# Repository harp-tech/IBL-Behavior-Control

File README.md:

# IBL Behavior Control (IBL BC)

Repository for the IBL's new behavior control system, based on Harp technology.

# Documentation

Manuals can be found in the folder *Manuals*

# Licensing

The code, designs, documentation, and photos available in this repository is free: you can redistribute it and/or modify it under the terms of the used license.
Each subdirectory will contain a license or, possibly, a set of licenses if it involves both hardware and software. Check files named LICENSE.

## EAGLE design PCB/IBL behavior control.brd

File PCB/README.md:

### Licensing
Copyright Filipe Carvalho 2020

<br />This work is licensed under a <a rel="license" href="http://creativecommons.org/licenses/by-nc-sa/3.0/igo/">Creative Commons Attribution-NonCommercial-ShareAlike 3.0 IGO License</a>.

If your are interested in obtaining a license to sell this device, please contact filipe@open-ephys.org

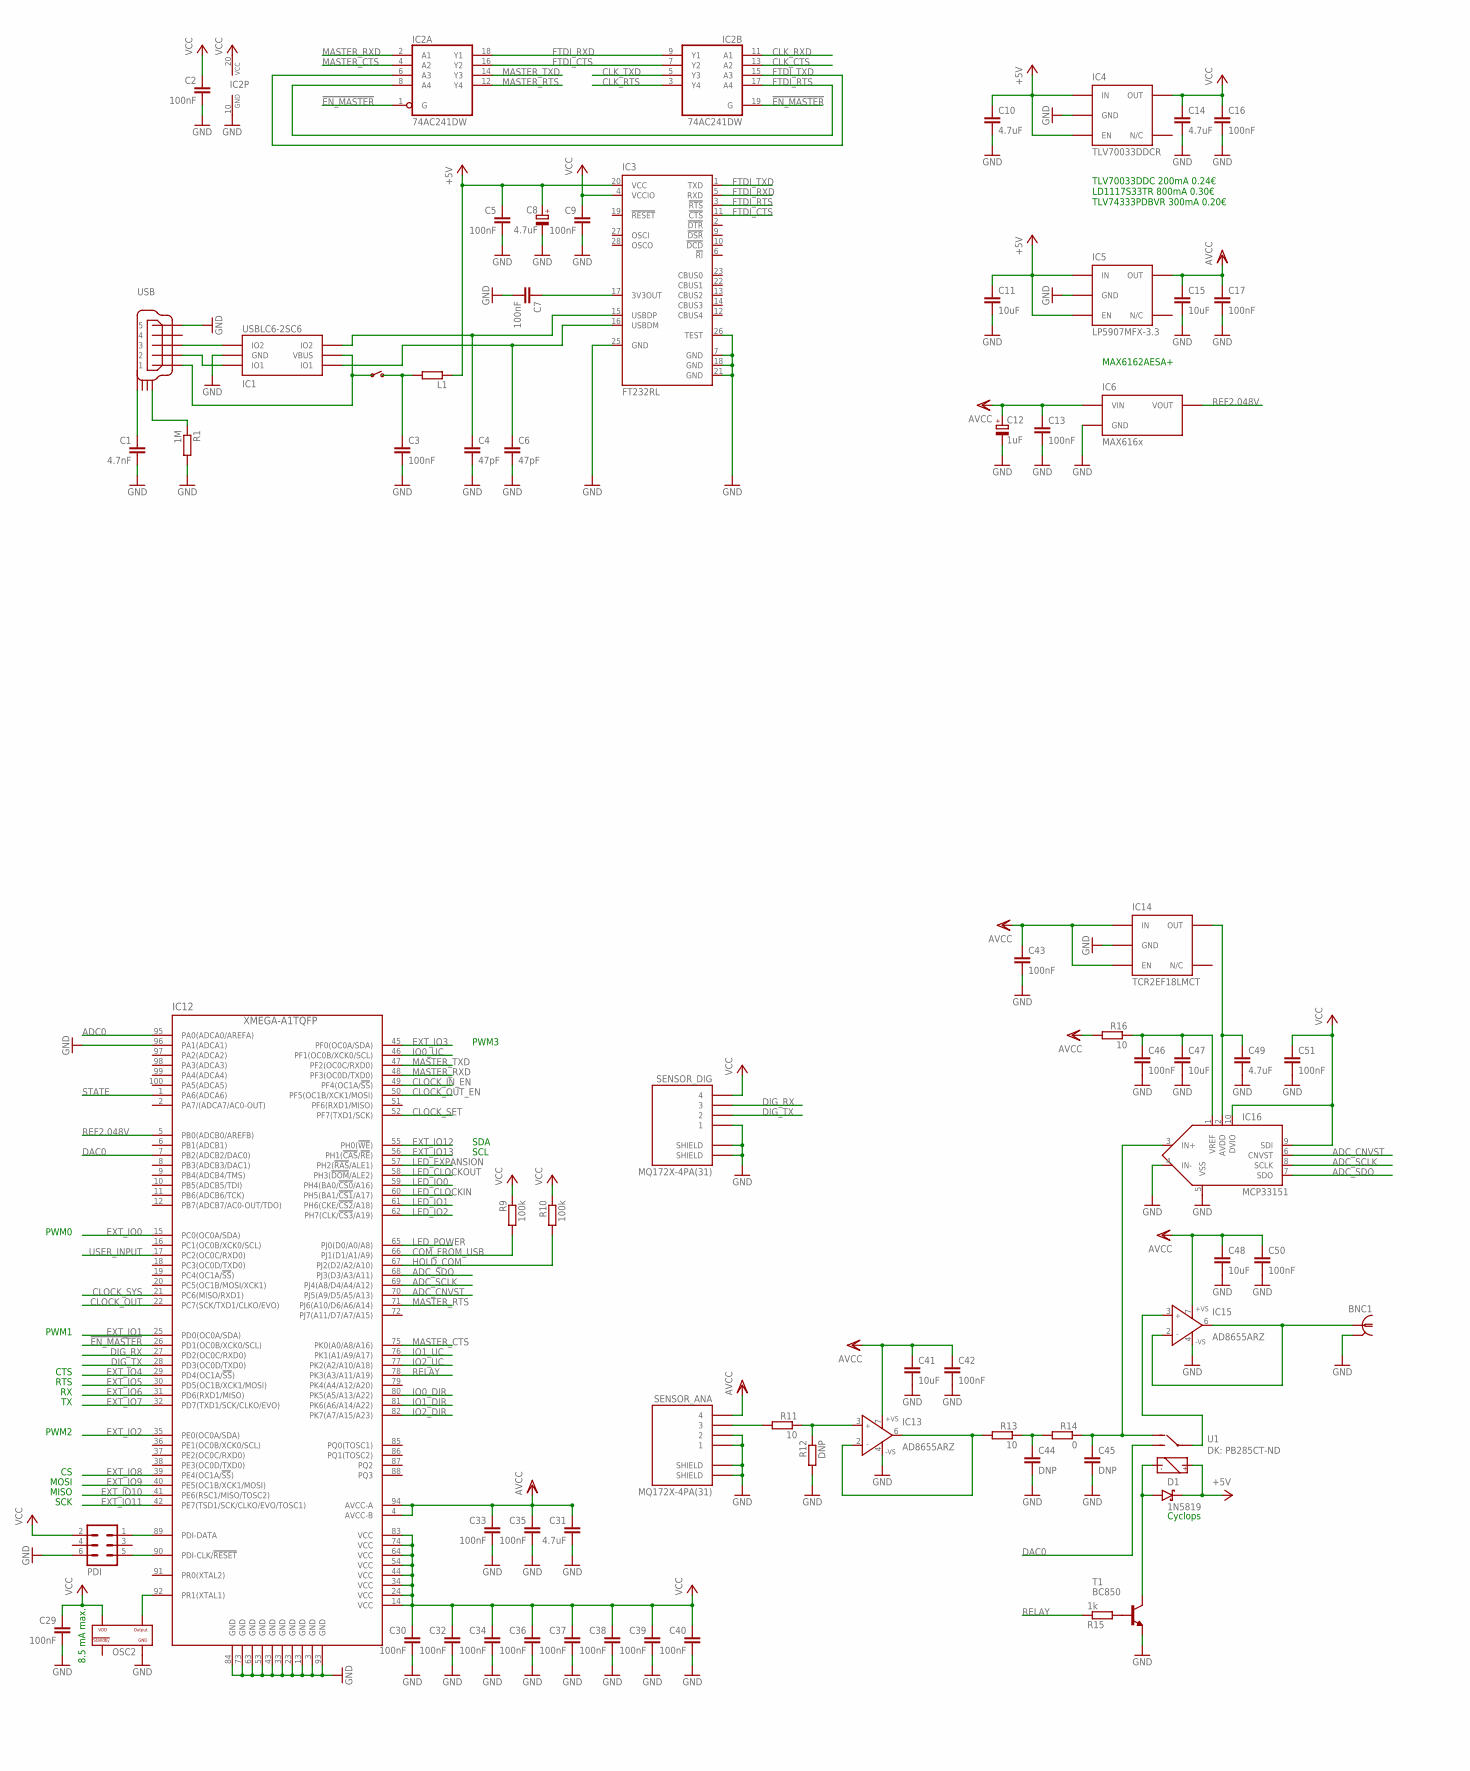
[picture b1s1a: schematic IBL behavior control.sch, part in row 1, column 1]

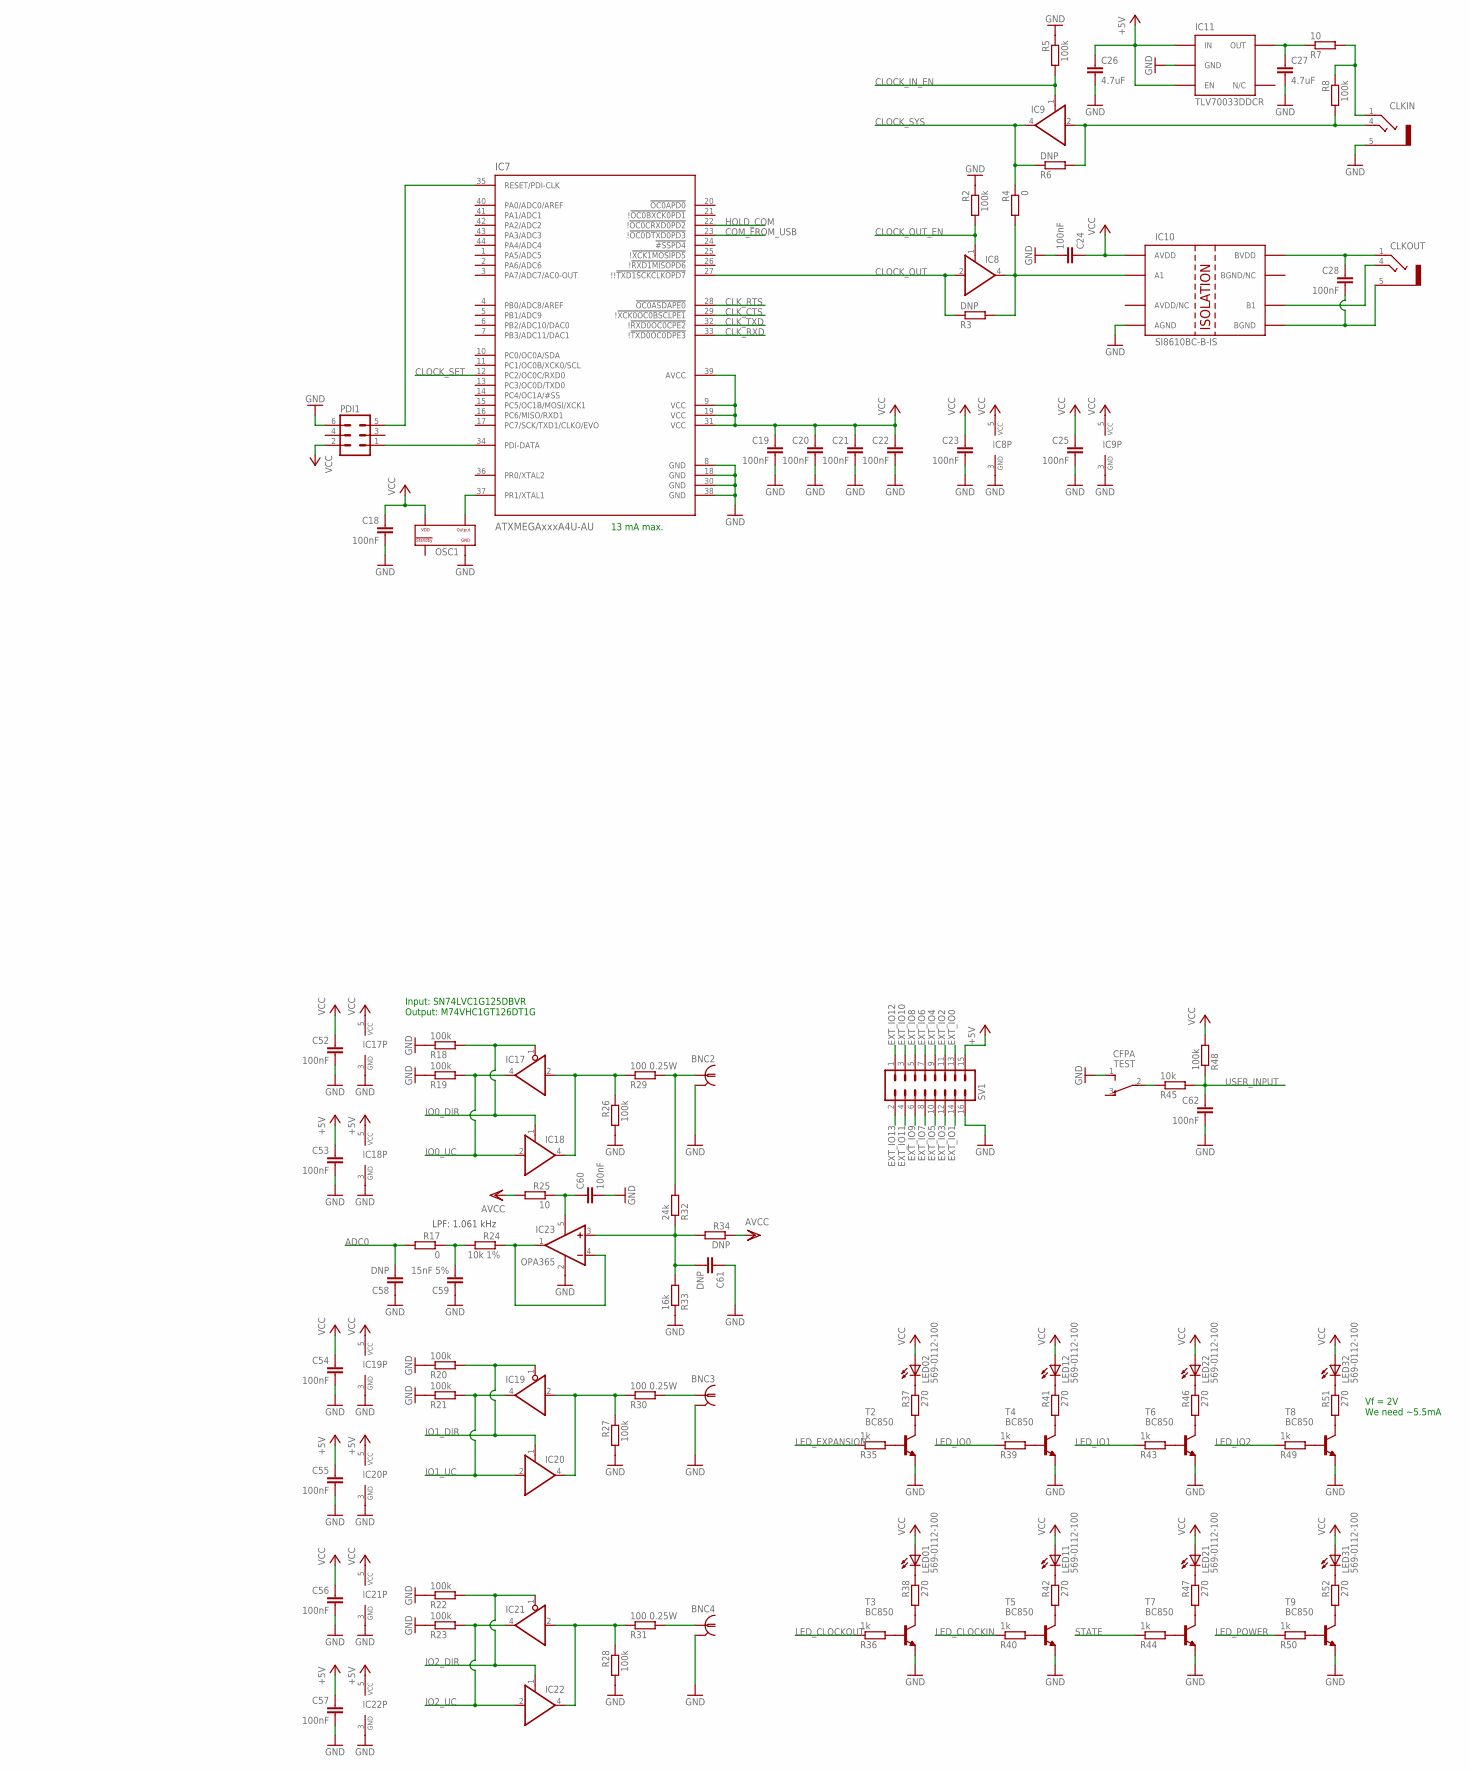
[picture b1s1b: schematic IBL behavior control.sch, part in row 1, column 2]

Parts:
BNC1, BNC2, BNC3, BNC4: BNC_0731000105; 0731000105
C1: 4.7nF; C0402
C2, C3, C5, C7, C9, C13, C16, C17, C18, C19, C20, C21, C22, C23, C24, C25, C28, C29, C30, C32, C33, C34, C35, C36, C37, C38, C39, C40, C42, C43, C46, C50, C51, C52, C53, C54, C55, C56, C57, C60, C62: 100nF; C0402
C4, C6: 47pF; C0402
C8: 4.7uF; A/3216-18W
C10, C14, C26, C27, C31, C49: 4.7uF; C0603
C11, C15, C41, C47, C48: 10uF; C0603
C12: 1uF; R/2012-12R
C44, C45, C58, C61: DNP; C0402
C59: 15nF 5%; C0402
CLKIN: STEREO_JACK; 35RASMT2BHNTRX
CLKOUT: STEREO_JACK; 35RASMT2BHNTRX
D1: 1N5819; SOD123
IC1: USBLC6-2SC6; SOT23-6L
IC2: 74AC241DW; SO20W
IC3: FT232RL; SSOP28
IC4, IC11: TLV70033DDCR; TSOT23-5
IC5: LP5907MFX-3.3; TSOT23-5
IC6: MAX616x; SO-08
IC7: ATXMEGAxxxA4U-AU; QFP80P1200X1200X120-44N
IC8, IC9, IC18, IC20, IC22: 74AHC1G126DCK; SC70-5
IC10: SI8610BC-B-IS; SO-08
IC12: XMEGA-A1TQFP; TQFP100
IC13, IC15: AD8655ARZ; SO8
IC14: TCR2EF18LMCT; TSOT23-5
IC16: MCP33151; MSOP10
IC17, IC19, IC21: 74AHC1G125DBV; SOT23-5
IC23: OPA365; SOT23-5
L1: ???; R0805
LED0, LED1, LED2, LED3: 569-0112-100; 569-011X-X00_LED_ARRAY
OSC1, OSC2: OSCILLATOR; OSCILLATOR_3.2X2.5
PDI, PDI1: MA03-2
R1: 1M; R0402
R2, R5, R8, R9, R10, R18, R19, R20, R21, R22, R23, R26, R27, R28, R48: 100k; R0402
R3, R6, R12, R34: DNP; R0402
R4, R14, R17: 0; R0402
R7, R11, R13, R16, R25: 10; R0402
R15, R35, R36, R39, R40, R43, R44, R49, R50: 1k; R0402
R24: 10k 1%; R0402
R29, R30, R31: 100 0.25W; R0603
R32: 24k; R0402
R33: 16k; R0402
R37, R38, R41, R42, R46, R47, R51, R52: 270; R0402
R45: 10k; R0402
SENSOR_ANA: MQ172X-4PA(31)
SENSOR_DIG: MQ172X-4PA(31)
SV1: ML16L
T1, T2, T3, T4, T5, T6, T7, T8, T9: BC850; SOT23
TEST: CFPA
U1: DK: PB285CT-ND; RELAY
USB: USB_MINI_B; 240-0002-1

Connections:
5VSWITCH: C3.1, L1.2
5VUSB: IC1.P$5 (VBUS), USB.P$1 (1)
!EN_MASTER: IC2.1 (G), IC2.19 (G), IC12.26 (PD1(OC0B/XCK0/SCL))
+5V: C5.1, C8.+, C10.1, C11.1, C26.1, C53.1, C55.1, C57.1, D1.C, IC3.20 (VCC), IC4.1 (IN), IC4.3 (EN), IC5.1 (IN), IC5.3 (EN), IC11.1 (IN), IC11.3 (EN), IC18.5 (VCC), IC20.5 (VCC), IC22.5 (VCC), L1.1, SV1.15, U1.3 (R+)
ADC0: C58.2, IC12.95 (PA0(ADCA0/AREFA)), R17.2
ADC_CNVST: IC12.70 (PJ5(A9/D5/A5/A13)), IC16.6 (CNVST)
ADC_SCLK: IC12.69 (PJ4(A8/D4/A4/A12)), IC16.8 (SCLK)
ADC_SDO: IC12.68 (PJ3(D3/A3/A11)), IC16.7 (SDO)
CLK_CTS: IC2.13 (A2), IC7.29 (!!XCK0OC0BSCLPE1)
CLK_RTS: IC2.3 (Y4), IC7.28 (!OC0ASDAPE0)
CLK_RXD: IC2.11 (A1), IC7.33 (!!TXD0OC0DPE3)
CLK_TXD: IC2.5 (Y3), IC7.32 (!!RXD0OC0CPE2)
CLOCK_IN_EN: IC9.1 (OE), IC12.49 (PF4(OC1A/!SS!)), R5.2
CLOCK_OUT: IC7.27 (!!!TXD1SCKCLKOPD7), IC8.2 (I), IC12.22 (PC7(SCK/TXD1/CLKO/EVO)), R3.1
CLOCK_OUT_EN: IC8.1 (OE), IC12.50 (PF5(OC1B/XCK1/MOSI)), R2.2
CLOCK_SET: IC7.12 (PC2/OC0C/RXD0), IC12.52 (PF7(TXD1/SCK))
CLOCK_SYS: IC9.4 (O), IC12.21 (PC6(MISO/RXD1)), R4.1, R6.1
COM_FROM_USB: IC7.23 (!!OC0DTXD0PD3), IC12.66 (PJ1(D1/A1/A9)), R9.2
DAC0: IC12.7 (PB2(ADCB2/DAC0)), U1.10 (NO)
DIG_RX: IC12.27 (PD2(OC0C/RXD0)), SENSOR_DIG.3
DIG_TX: IC12.28 (PD3(OC0D/TXD0)), SENSOR_DIG.2
EXT_IO0: IC12.15 (PC0(OC0A/SDA)), SV1.13
EXT_IO1: IC12.25 (PD0(OC0A/SDA)), SV1.14
EXT_IO2: IC12.35 (PE0(OC0A/SDA)), SV1.11
EXT_IO3: IC12.45 (PF0(OC0A/SDA)), SV1.12
EXT_IO4: IC12.29 (PD4(OC1A/!SS!)), SV1.9
EXT_IO5: IC12.30 (PD5(OC1B/XCK1/MOSI)), SV1.10
EXT_IO6: IC12.31 (PD6(RXD1/MISO)), SV1.7
EXT_IO7: IC12.32 (PD7(TXD1/SCK/CLKO/EVO)), SV1.8
EXT_IO8: IC12.39 (PE4(OC1A/!SS!)), SV1.5
EXT_IO9: IC12.40 (PE5(OC1B/XCK1/MOSI)), SV1.6
EXT_IO10: IC12.41 (PE6(RSC1/MISO/TOSC2)), SV1.3
EXT_IO11: IC12.42 (PE7(TSD1/SCK/CLKO/EVO/TOSC1)), SV1.4
EXT_IO12: IC12.55 (PH0(!WE!)), SV1.1
EXT_IO13: IC12.56 (PH1(!CAS!/!RE!)), SV1.2
FTDI_CTS: IC2.7 (Y2), IC2.16 (Y2), IC3.11 (!CTS)
FTDI_RTS: IC2.8 (A4), IC2.17 (A4), IC3.3 (!RTS)
FTDI_RXD: IC2.9 (Y1), IC2.18 (Y1), IC3.5 (RXD)
FTDI_TXD: IC2.6 (A3), IC2.15 (A3), IC3.1 (TXD)
GND: BNC1.2, BNC1.3 (2), BNC2.2, BNC2.3 (2), BNC3.2, BNC3.3 (2), BNC4.2, BNC4.3 (2), C1.2, C2.2, C3.2, C4.2, C5.2, C6.2, C7.2, C8.-, C9.2, C10.2, C11.2, C12.-, C13.2, C14.2, C15.2, C16.2, C17.2, C18.2, C19.2, C20.2, C21.2, C22.2, C23.2, C24.2, C25.2, C26.2, C27.2, C29.2, C30.2, C31.2, C32.2, C33.2, C34.2, C35.2, C36.2, C37.2, C38.2, C39.2, C40.2, C41.2, C42.2, C43.2, C44.2, C45.2, C46.2, C47.2, C48.2, C49.2, C50.2, C51.2, C52.2, C53.2, C54.2, C55.2, C56.2, C57.2, C58.1, C59.1, C60.2, C61.1, C62.2, CLKIN.5, IC1.P$2 (GND), IC2.10 (GND), IC3.7 (GND), IC3.18 (GND), IC3.21 (GND), IC3.25 (GND), IC3.26 (TEST), IC4.2 (GND), IC5.2 (GND), IC6.4 (GND), IC7.8 (GND), IC7.18 (GND), IC7.30 (GND), IC7.38 (GND), IC8.3 (GND), IC9.3 (GND), IC10.4 (AGND), IC11.2 (GND), IC12.3 (GND), IC12.13 (GND), IC12.23 (GND), IC12.33 (GND), IC12.43 (GND), IC12.53 (GND), IC12.63 (GND), IC12.73 (GND), IC12.84 (GND), IC12.93 (GND), IC12.96 (PA1(ADCA1)), IC13.4 (-VS), IC14.2 (GND), IC15.4 (-VS), IC16.4 (IN-), IC16.5 (VSS), IC17.3 (GND), IC18.3 (GND), IC19.3 (GND), IC20.3 (GND), IC21.3 (GND), IC22.3 (GND), IC23.2 (V-), OSC1.P$2 (GND), OSC2.P$2 (GND), PDI.6, PDI1.6, R1.2, R2.1, R5.1, R12.2, R18.1, R19.1, R20.1, R21.1, R22.1, R23.1, R26.2, R27.2, R28.2, R33.1, SENSOR_ANA.1, SENSOR_ANA.2, SENSOR_ANA.SHIELD1 (SHIELD), SENSOR_ANA.SHIELD2 (SHIELD), SENSOR_DIG.1, SENSOR_DIG.SHIELD1 (SHIELD), SENSOR_DIG.SHIELD2 (SHIELD), SV1.16, T1.2 (E), T2.2 (E), T3.2 (E), T4.2 (E), T5.2 (E), T6.2 (E), T7.2 (E), T8.2 (E), T9.2 (E), TEST.1 (3), USB.P$5 (5)
GND_ISO: C28.2, CLKOUT.5, IC10.5 (BGND)
HOLD_COM: IC7.22 (!!OC0CRXD0PD2), IC12.67 (PJ2(D2/A2/A10)), R10.2
IO0_ANALOG: C59.2, R17.1, R24.2
IO0_DIR: IC12.80 (PK5(A5/A13/A22)), IC17.1 (OE), IC18.1 (OE), R18.2
IO0_UC: IC12.46 (PF1(OC0B/XCK0/SCL)), IC17.4 (O), IC18.2 (I), R19.2
IO1_DIR: IC12.81 (PK6(A6/A14/A22)), IC19.1 (OE), IC20.1 (OE), R20.2
IO1_UC: IC12.76 (PK1(A1/A9/A17)), IC19.4 (O), IC20.2 (I), R21.2
IO2_DIR: IC12.82 (PK7(A7/A15/A23)), IC21.1 (OE), IC22.1 (OE), R22.2
IO2_UC: IC12.77 (PK2(A2/A10/A18)), IC21.4 (O), IC22.2 (I), R23.2
LED_CLOCKIN: IC12.60 (PH5(BA1/!CS1!/A17)), R40.1
LED_CLOCKOUT: IC12.58 (PH3(!DOM!/ALE2)), R36.1
LED_EXPANSION: IC12.57 (PH2(!RAS!/ALE1)), R35.1
LED_IO0: IC12.59 (PH4(BA0/!CS0!/A16)), R39.1
LED_IO1: IC12.61 (PH6(CKE/!CS2!/A18)), R43.1
LED_IO2: IC12.62 (PH7(CLK/!CS3!/A19)), R49.1
LED_POWER: IC12.65 (PJ0(D0/A0/A8)), R50.1
MASTER_CTS: IC2.4 (A2), IC12.75 (PK0(A0/A8/A16))
MASTER_RTS: IC2.12 (Y4), IC12.71 (PJ6(A10/D6/A6/A14))
MASTER_RXD: IC2.2 (A1), IC12.48 (PF3(OC0D/TXD0))
MASTER_TXD: IC2.14 (Y3), IC12.47 (PF2(OC0C/RXD0))
unnamed: CLKOUT.4, IC10.6 (B1)
unnamed: R35.2, T2.1 (B)
unnamed: LED0.C2 (C), R37.1
unnamed: C28.1, CLKOUT.1, IC10.8 (BVDD)
unnamed: IC17.2 (I), IC18.4 (O), R26.1, R29.1
unnamed: R37.2, T2.3 (C)
unnamed: BNC2.1, R29.2, R32.2
unnamed: IC19.2 (I), IC20.4 (O), R27.1, R30.1
unnamed: BNC3.1, R30.2
unnamed: IC21.2 (I), IC22.4 (O), R28.1, R31.1
unnamed: BNC4.1, R31.2
unnamed: R36.2, T3.1 (B)
unnamed: R43.2, T6.1 (B)
unnamed: R38.2, T3.3 (C)
unnamed: R39.2, T4.1 (B)
unnamed: LED3.C1 (C), R52.1
unnamed: R41.2, T4.3 (C)
unnamed: R40.2, T5.1 (B)
unnamed: R46.2, T6.3 (C)
unnamed: R42.2, T5.3 (C)
unnamed: LED3.C2 (C), R51.1
unnamed: R44.2, T7.1 (B)
unnamed: R47.2, T7.3 (C)
unnamed: R49.2, T8.1 (B)
unnamed: R51.2, T8.3 (C)
unnamed: R50.2, T9.1 (B)
unnamed: R52.2, T9.3 (C)
unnamed: LED1.C2 (C), R41.1
unnamed: LED2.C2 (C), R46.1
unnamed: LED1.C1 (C), R42.1
unnamed: LED2.C1 (C), R47.1
unnamed: R45.1, TEST.2
unnamed: C60.1, IC23.5 (V+), R25.1
unnamed: LED0.C1 (C), R38.1
unnamed: IC13.2 (IN-), IC13.6 (OUT), R13.2
unnamed: C7.1, IC3.17 (3V3OUT)
unnamed: IC13.3 (IN+), R11.1, R12.1
unnamed: IC1.P$1 (IO1), USB.P$2 (2)
unnamed: CLKIN.1, R7.2, R8.1
unnamed: C27.1, IC11.5 (OUT), R7.1
unnamed: IC8.4 (O), IC10.2 (A1), R3.2, R4.2
unnamed: C49.1, IC14.5 (OUT), IC16.2 (AVDD)
unnamed: C44.1, R13.1, R14.2
unnamed: C45.1, IC16.3 (IN+), R14.1, U1.1 (NC)
unnamed: BNC1.1, IC15.2 (IN-), IC15.6 (OUT)
unnamed: C46.1, C47.1, IC16.1 (VREF), R16.1
unnamed: IC1.P$3 (IO2), USB.P$3 (3)
unnamed: IC15.3 (IN+), U1.5 (IN)
unnamed: R11.2, SENSOR_ANA.3
unnamed: R15.2, T1.1 (B)
unnamed: D1.A, T1.3 (C), U1.8 (R-)
unnamed: IC23.1 (OUT), IC23.4 (-IN), R24.1
unnamed: C1.1, USB.SHIELD_4
unnamed: R1.1, USB.SHIELD_1
unnamed: C61.2, IC23.3 (+IN), R32.1, R33.2, R34.2
OSC1: IC12.92 (PR1(XTAL1)), OSC2.P$3 (OUTPUT)
OSC2: IC7.37 (PR1/XTAL1), OSC1.P$3 (OUTPUT)
PDI-CLK: IC7.35 (RESET/PDI-CLK), PDI1.5
PDI-DATA: IC7.34 (PDI-DATA), PDI1.1
PDI_CLK: IC12.90 (PDI-CLK/!RESET), PDI.5
PDI_DATA: IC12.89 (PDI-DATA), PDI.1
REF2.048V: IC6.6 (VOUT), IC12.5 (PB0(ADCB0/AREFB))
RELAY: IC12.78 (PK3(A3/A11/A19)), R15.1
STATE: IC12.1 (PA6(ADCA6)), R44.1
SYNCIN: CLKIN.4, IC9.2 (I), R6.2, R8.2
USBDM: C6.1, IC1.P$6 (IO1), IC3.16 (USBDM)
USBDP: C4.1, IC1.P$4 (IO2), IC3.15 (USBDP)
USER_INPUT: C62.1, IC12.17 (PC2(OC0C/RXD0)), R45.2, R48.1
VCC: C2.1, C9.1, C14.1, C16.1, C18.1, C19.1, C20.1, C21.1, C22.1, C23.1, C24.1, C25.1, C29.1, C30.1, C32.1, C34.1, C36.1, C37.1, C38.1, C39.1, C40.1, C51.1, C52.1, C54.1, C56.1, IC2.20 (VCC), IC3.4 (VCCIO), IC4.5 (OUT), IC7.9 (VCC), IC7.19 (VCC), IC7.31 (VCC), IC7.39 (AVCC), IC8.5 (VCC), IC9.5 (VCC), IC10.1 (AVDD), IC12.14 (VCC), IC12.24 (VCC), IC12.34 (VCC), IC12.44 (VCC), IC12.54 (VCC), IC12.64 (VCC), IC12.74 (VCC), IC12.83 (VCC), IC16.9 (SDI), IC16.10 (DVIO), IC17.5 (VCC), IC19.5 (VCC), IC21.5 (VCC), LED0.A1 (A), LED0.A2 (A), LED1.A1 (A), LED1.A2 (A), LED2.A1 (A), LED2.A2 (A), LED3.A1 (A), LED3.A2 (A), OSC1.P$4 (VDD), OSC2.P$4 (VDD), PDI.2, PDI1.2, R9.1, R10.1, R48.2, SENSOR_DIG.4
VDD: C12.+, C13.1, C15.1, C17.1, C31.1, C33.1, C35.1, C41.1, C42.1, C43.1, C48.1, C50.1, IC5.5 (OUT), IC6.2 (VIN), IC12.4 (AVCC-B), IC12.94 (AVCC-A), IC13.7 (+VS), IC14.1 (IN), IC14.3 (EN), IC15.7 (+VS), R16.2, R25.2, R34.1, SENSOR_ANA.4

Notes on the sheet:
RTS
CTS
PWM2
PWM1
MOSI
MISO
SCK
PWM0
PWM3
SDA
SCL
Input: SN74LVC1G125DBVR Output: M74VHC1GT126DT1G
Vf = 2V We need ~5.5mA
8.5 mA max.
13 mA max.
TLV70033DDC 200mA 0.24€ LD1117S33TR 800mA 0.30€ TLV74333PDBVR 300mA 0.20€
LPF: 1.061 kHz
MAX6162AESA+
Cyclops

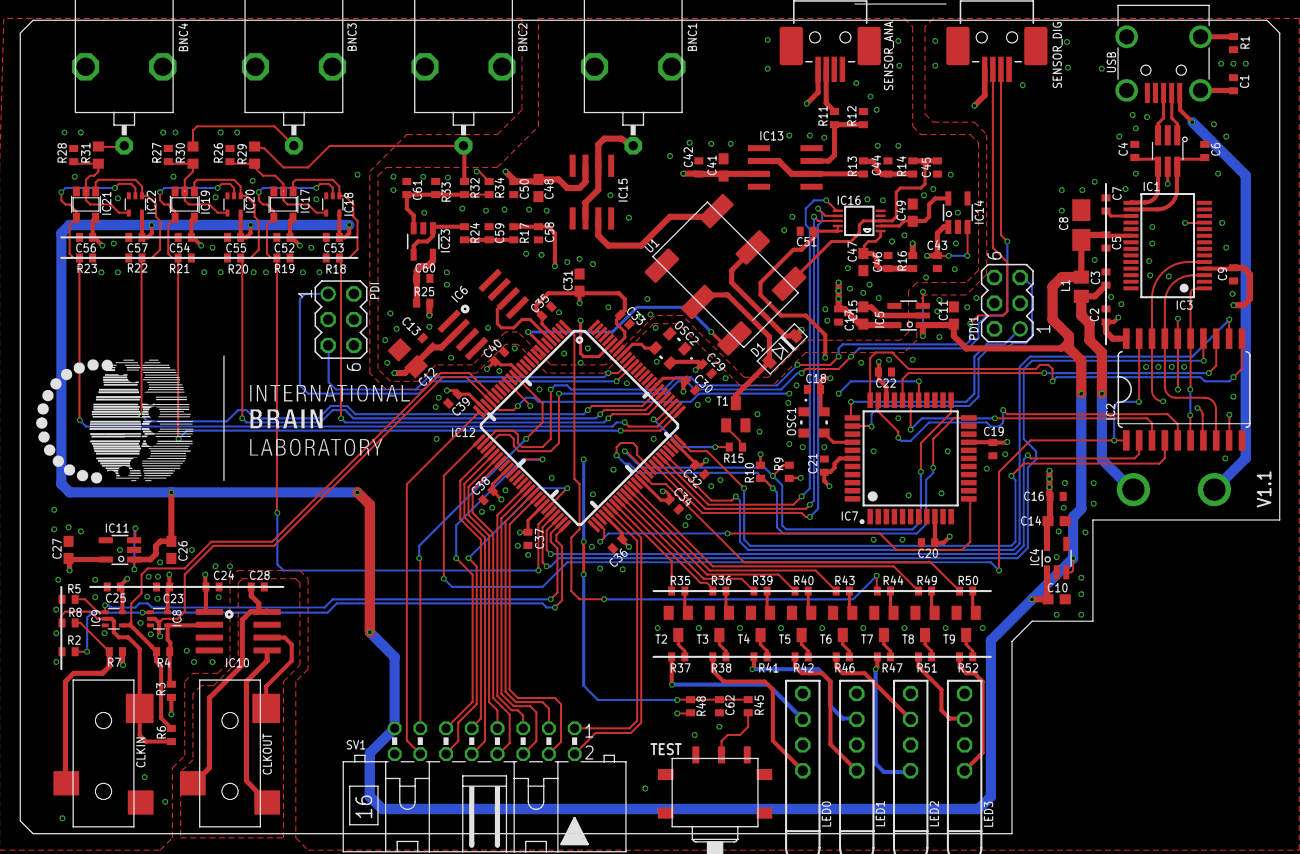
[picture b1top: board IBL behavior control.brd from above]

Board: 4 copper layers, 124.5 x 80.4 mm, 168 parts (0 on the bottom side), 130 nets.

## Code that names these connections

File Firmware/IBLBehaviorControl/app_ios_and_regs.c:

#include <avr/io.h>
#include "hwbp_core_types.h"
#include "app_ios_and_regs.h"

/************************************************************************/
/* Configure and initialize IOs                                         */
/************************************************************************/
void init_ios(void)
{	/* Configure input pins */
	io_pin2in(&PORTJ, 3, PULL_IO_TRISTATE, SENSE_IO_EDGES_BOTH);         // ADC_SDO
	io_pin2in(&PORTC, 2, PULL_IO_TRISTATE, SENSE_IO_EDGES_BOTH);         // USER
	io_pin2in(&PORTF, 1, PULL_IO_TRISTATE, SENSE_IO_EDGES_BOTH);         // IO0
	io_pin2in(&PORTK, 1, PULL_IO_TRISTATE, SENSE_IO_EDGES_BOTH);         // IO1
	io_pin2in(&PORTK, 2, PULL_IO_TRISTATE, SENSE_IO_EDGES_BOTH);         // IO2

	/* Configure input interrupts */
	io_set_int(&PORTC, INT_LEVEL_LOW, 0, (1<<2), false);                 // USER
	io_set_int(&PORTF, INT_LEVEL_LOW, 0, (1<<1), false);                 // IO0
	io_set_int(&PORTK, INT_LEVEL_LOW, 0, (1<<1), false);                 // IO1
	io_set_int(&PORTK, INT_LEVEL_LOW, 1, (1<<2), false);                 // IO2

	/* Configure output pins */
	io_pin2out(&PORTF, 4, OUT_IO_DIGITAL, IN_EN_IO_EN);                  // CLOCK_IN_EN
	io_pin2out(&PORTF, 5, OUT_IO_DIGITAL, IN_EN_IO_EN);                  // CLOCK_OUT_EN
	io_pin2out(&PORTK, 3, OUT_IO_DIGITAL, IN_EN_IO_EN);                  // RELAY
	io_pin2out(&PORTJ, 4, OUT_IO_DIGITAL, IN_EN_IO_EN);                  // ADC_SCLK
	io_pin2out(&PORTJ, 5, OUT_IO_DIGITAL, IN_EN_IO_EN);                  // ADC_CNVST
	io_pin2out(&PORTD, 1, OUT_IO_DIGITAL, IN_EN_IO_EN);                  // EN_MASTER
	io_pin2out(&PORTH, 2, OUT_IO_DIGITAL, IN_EN_IO_EN);                  // LED_CLKIN
	io_pin2out(&PORTH, 4, OUT_IO_DIGITAL, IN_EN_IO_EN);                  // LED_IO0
	io_pin2out(&PORTH, 6, OUT_IO_DIGITAL, IN_EN_IO_EN);                  // LED_IO1
	io_pin2out(&PORTH, 7, OUT_IO_DIGITAL, IN_EN_IO_EN);                  // LED_IO2
	io_pin2out(&PORTH, 3, OUT_IO_DIGITAL, IN_EN_IO_EN);                  // LED_SLAVE
	io_pin2out(&PORTH, 5, OUT_IO_DIGITAL, IN_EN_IO_EN);                  // LED_MASTER
	io_pin2out(&PORTA, 6, OUT_IO_DIGITAL, IN_EN_IO_EN);                  // LED_STATE
	io_pin2out(&PORTJ, 0, OUT_IO_DIGITAL, IN_EN_IO_EN);                  // LED_POWER
	io_pin2out(&PORTF, 1, OUT_IO_DIGITAL, IN_EN_IO_EN);                  // IO0
	io_pin2out(&PORTK, 1, OUT_IO_DIGITAL, IN_EN_IO_EN);                  // IO1
	io_pin2out(&PORTK, 2, OUT_IO_DIGITAL, IN_EN_IO_EN);                  // IO2
	io_pin2out(&PORTK, 5, OUT_IO_DIGITAL, IN_EN_IO_EN);                  // IO0_DIR
	io_pin2out(&PORTK, 6, OUT_IO_DIGITAL, IN_EN_IO_EN);                  // IO1_DIR
	io_pin2out(&PORTK, 7, OUT_IO_DIGITAL, IN_EN_IO_EN);                  // IO2_DIR

	/* Initialize output pins */
	clr_CLOCK_IN_EN;
	clr_CLOCK_OUT_EN;
	clr_RELAY;
	clr_ADC_SCLK;
	clr_ADC_CNVST;
	clr_EN_MASTER;
	clr_LED_CLKIN;
	clr_LED_IO0;
	clr_LED_IO1;
	clr_LED_IO2;
	clr_LED_SLAVE;
	clr_LED_MASTER;
	clr_LED_STATE;
	clr_LED_POWER;
	clr_IO0;
	clr_IO1;
	clr_IO2;
	clr_IO0_DIR;
	clr_IO1_DIR;
	clr_IO2_DIR;
}

/************************************************************************/
/* Registers' stuff                                                     */
/************************************************************************/
AppRegs app_regs;

uint8_t app_regs_type[] = {
	TYPE_U16,
	TYPE_I16,
	TYPE_U8,
	TYPE_U8,
	TYPE_U8,
	TYPE_U8,
	TYPE_U8,
	TYPE_U8,
	TYPE_U8,
	TYPE_U8,
	TYPE_U16,
	TYPE_U16,
	TYPE_U16,
	TYPE_U16,
	TYPE_U8,
	TYPE_U16,
	TYPE_U16,
	TYPE_U16,
	TYPE_U16,
	TYPE_U8,
	TYPE_U16,
	TYPE_U16,
	TYPE_U16,
	TYPE_U16,
	TYPE_U8,
	TYPE_U16,
	TYPE_U16,
	TYPE_U16,
	TYPE_U16,
	TYPE_U8,
	TYPE_I16,
	TYPE_U16,
	TYPE_I16,
	TYPE_U16,
	TYPE_U8,
	TYPE_I16,
	TYPE_U16,
	TYPE_I16,
	TYPE_U16,
	TYPE_U8,
	TYPE_U8,
	TYPE_U16,
	TYPE_I16
};

uint16_t app_regs_n_elements[] = {
	1,
	4,
	1,
	1,
	1,
	1,
	1,
	1,
	1,
	1,
	1,
	1,
	1,
	1,
	1,
	1,
	1,
	1,
	1,
	1,
	1,
	1,
	1,
	1,
	1,
	1,
	1,
	1,
	1,
	1,
	1,
	1,
	1,
	1,
	1,
	1,
	1,
	1,
	1,
	1,
	1,
	1,
	1
};

uint8_t *app_regs_pointer[] = {
	(uint8_t*)(&app_regs.REG_CONFIG),
	(uint8_t*)(app_regs.REG_DATA_STREAM),
	(uint8_t*)(&app_regs.REG_INPUTS),
	(uint8_t*)(&app_regs.REG_INPUT_IO0_CONFIG),
	(uint8_t*)(&app_regs.REG_INPUT_IO1_CONFIG),
	(uint8_t*)(&app_regs.REG_INPUT_IO2_CONFIG),
	(uint8_t*)(&app_regs.REG_OUTPUT_SET),
	(uint8_t*)(&app_regs.REG_OUTPUT_CLEAR),
	(uint8_t*)(&app_regs.REG_OUTPUT_TOGGLE),
	(uint8_t*)(&app_regs.REG_OUTPUT_WRITE),
	(uint8_t*)(&app_regs.REG_ANA_SENSOR_TH0_HIGH),
	(uint8_t*)(&app_regs.REG_ANA_SENSOR_TH0_HIGH_MS),
	(uint8_t*)(&app_regs.REG_ANA_SENSOR_TH0_LOW),
	(uint8_t*)(&app_regs.REG_ANA_SENSOR_TH0_LOW_MS),
	(uint8_t*)(&app_regs.REG_ANA_SENSOR_TH0_EVT_CONF),
	(uint8_t*)(&app_regs.REG_ANA_SENSOR_TH1_HIGH),
	(uint8_t*)(&app_regs.REG_ANA_SENSOR_TH1_HIGH_MS),
	(uint8_t*)(&app_regs.REG_ANA_SENSOR_TH1_LOW),
	(uint8_t*)(&app_regs.REG_ANA_SENSOR_TH1_LOW_MS),
	(uint8_t*)(&app_regs.REG_ANA_SENSOR_TH1_EVT_CONF),
	(uint8_t*)(&app_regs.REG_ANA_INPUT_TH0_HIGH),
	(uint8_t*)(&app_regs.REG_ANA_INPUT_TH0_HIGH_MS),
	(uint8_t*)(&app_regs.REG_ANA_INPUT_TH0_LOW),
	(uint8_t*)(&app_regs.REG_ANA_INPUT_TH0_LOW_MS),
	(uint8_t*)(&app_regs.REG_ANA_INPUT_TH0_EVT_CONF),
	(uint8_t*)(&app_regs.REG_ANA_INPUT_TH1_HIGH),
	(uint8_t*)(&app_regs.REG_ANA_INPUT_TH1_HIGH_MS),
	(uint8_t*)(&app_regs.REG_ANA_INPUT_TH1_LOW),
	(uint8_t*)(&app_regs.REG_ANA_INPUT_TH1_LOW_MS),
	(uint8_t*)(&app_regs.REG_ANA_INPUT_TH1_EVT_CONF),
	(uint8_t*)(&app_regs.REG_ENCODER_TH0_HIGH),
	(uint8_t*)(&app_regs.REG_ENCODER_TH0_HIGH_MS),
	(uint8_t*)(&app_regs.REG_ENCODER_TH0_LOW),
	(uint8_t*)(&app_regs.REG_ENCODER_TH0_LOW_MS),
	(uint8_t*)(&app_regs.REG_ENCODER_TH0_EVT_CONF),
	(uint8_t*)(&app_regs.REG_ENCODER_TH1_HIGH),
	(uint8_t*)(&app_regs.REG_ENCODER_TH1_HIGH_MS),
	(uint8_t*)(&app_regs.REG_ENCODER_TH1_LOW),
	(uint8_t*)(&app_regs.REG_ENCODER_TH1_LOW_MS),
	(uint8_t*)(&app_regs.REG_ENCODER_TH1_EVT_CONF),
	(uint8_t*)(&app_regs.REG_TH_ENABLE_EVENTS),
	(uint8_t*)(&app_regs.REG_WRITE_AO),
	(uint8_t*)(&app_regs.REG_ENCODER)
};

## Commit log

2020-06-28 Updated briefly the repository description.
2020-07-12 Added the licenses.
2020-07-12 Added firmware files.
2020-07-12 Added PCB files.
2020-07-12 Added photos of the device.
2020-07-12 Added photo of the device to README file.
2020-07-12 Removed unused files.
2020-08-02 Updated registers' default and improved LED indication.
2020-08-02 Updated firmware license.
2020-08-02 Corrected register CONFIG and implemented the digital inputs' events.
2020-08-02 Corrected data stream control when user changes the timings of the thresholds.
2020-08-02 Added images of the logos used in the PCBs and updated the PCBs' license to NonCommercial.
2020-08-02 Added license to photos. Minor edits on some README files.
2020-08-02 Added control registers manual.
2020-08-02 Added logos.
2020-08-02 Updated logos' names.
2020-08-03 Added Bonsai code.
2020-08-09 Minor edit on README.md and corrected device ID.
2020-08-09 Fixed front panel measurements.
2020-08-09 Separated digital output commands into a new command node.
2020-08-14 Added "Bonsai" word to tags and updated Guid
2020-08-14 Removed common values silkscreen
2020-08-14 Implemented reading of the USER INPUT button
2022-10-05 Replaced an obsolete component.
2022-10-05 Minor correction.
